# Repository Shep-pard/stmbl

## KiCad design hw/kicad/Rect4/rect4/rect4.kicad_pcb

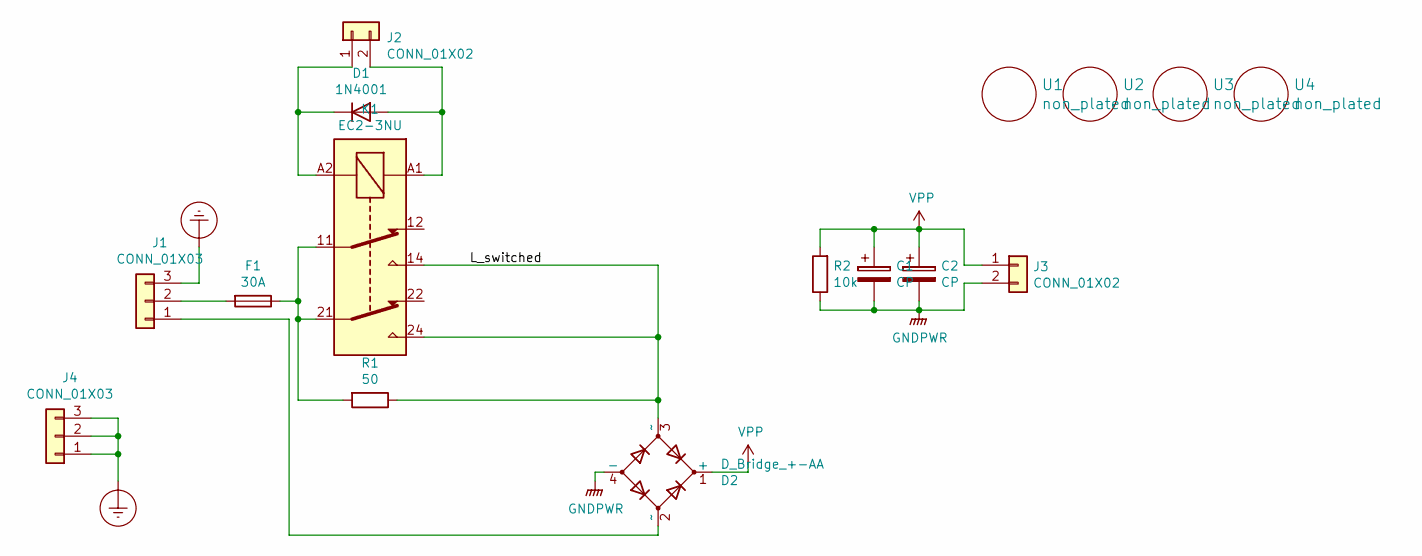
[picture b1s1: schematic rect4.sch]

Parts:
C1, C2: CP; C_Radial_D26_L45_P10
D1: 1N4001; D_DO-41_SOD81_P10.16mm_Horizontal
D2: D_Bridge_+-AA; Diode_Bridge_Vishay_KBU
F1: 30A; Fuse_Littelfuse_395Series
J1, J4: CONN_01X03; RM5.08_1x3
J2: CONN_01X02; RM3.5_1x2
J3: CONN_01X02; RM5.08_1x2
K1: EC2-3NU; Relay_DPDT_Finder_40.52
R1: 50; R_Axial_Power_L25.0mm_W9.0mm_P27.94mm
R2: 10k; R_Axial_DIN0207_L6.3mm_D2.5mm_P7.62mm_Horizontal
U1, U2, U3, U4: non_plated; non_plated_3mm

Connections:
/L_switched: D2.3 (~~), K1.14, K1.24, R1.1
Earth_Protective: J1.3, J4.1, J4.2, J4.3
GNDPWR: C1.2, C2.2, D2.4 (-), J3.2, R2.1
unnamed: D1.1 (K), J2.1, K1.A2
unnamed: D1.2 (A), J2.2, K1.A1
unnamed: D2.2 (~~), J1.1
unnamed: F1.1, K1.11, K1.21, R1.2
unnamed: F1.2, J1.2
VPP: C1.1, C2.1, D2.1 (+), J3.1, R2.2

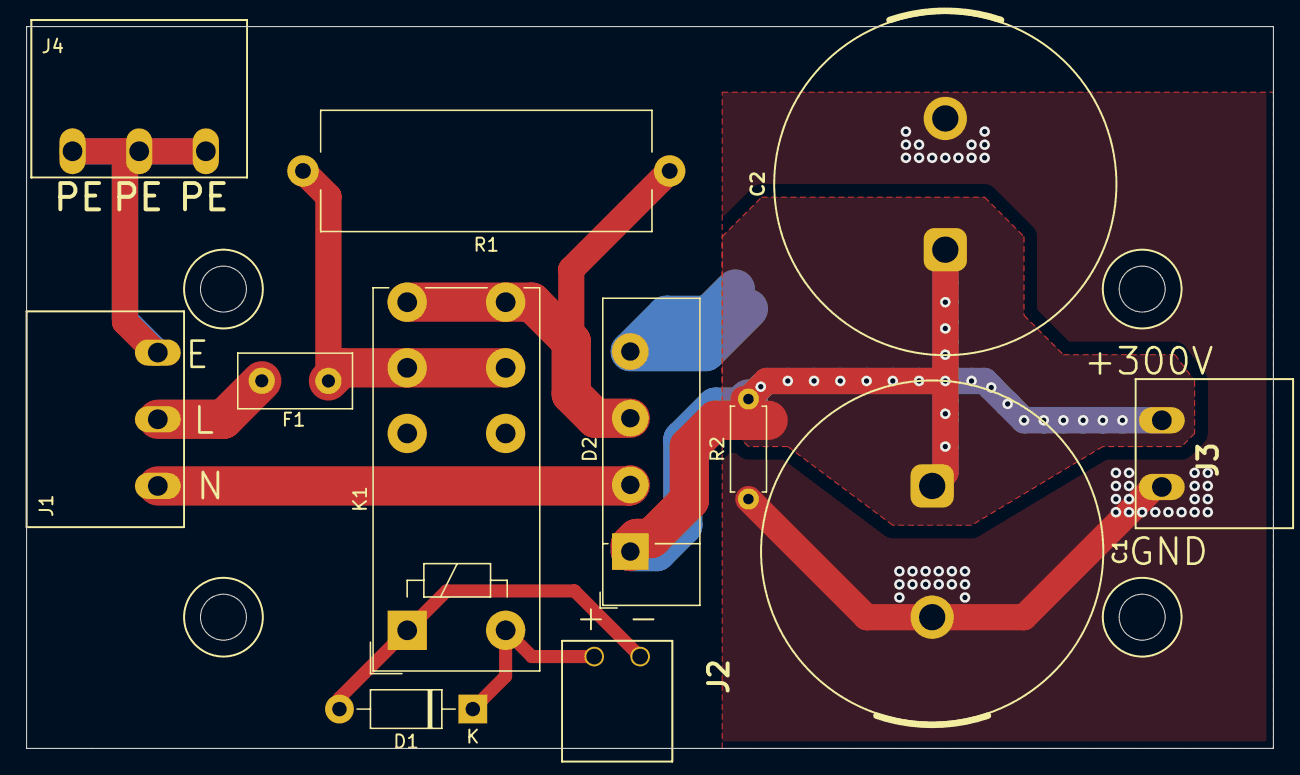
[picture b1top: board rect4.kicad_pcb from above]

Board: 2 copper layers, 95.0 x 55.0 mm, 16 parts (0 on the bottom side), 9 nets.

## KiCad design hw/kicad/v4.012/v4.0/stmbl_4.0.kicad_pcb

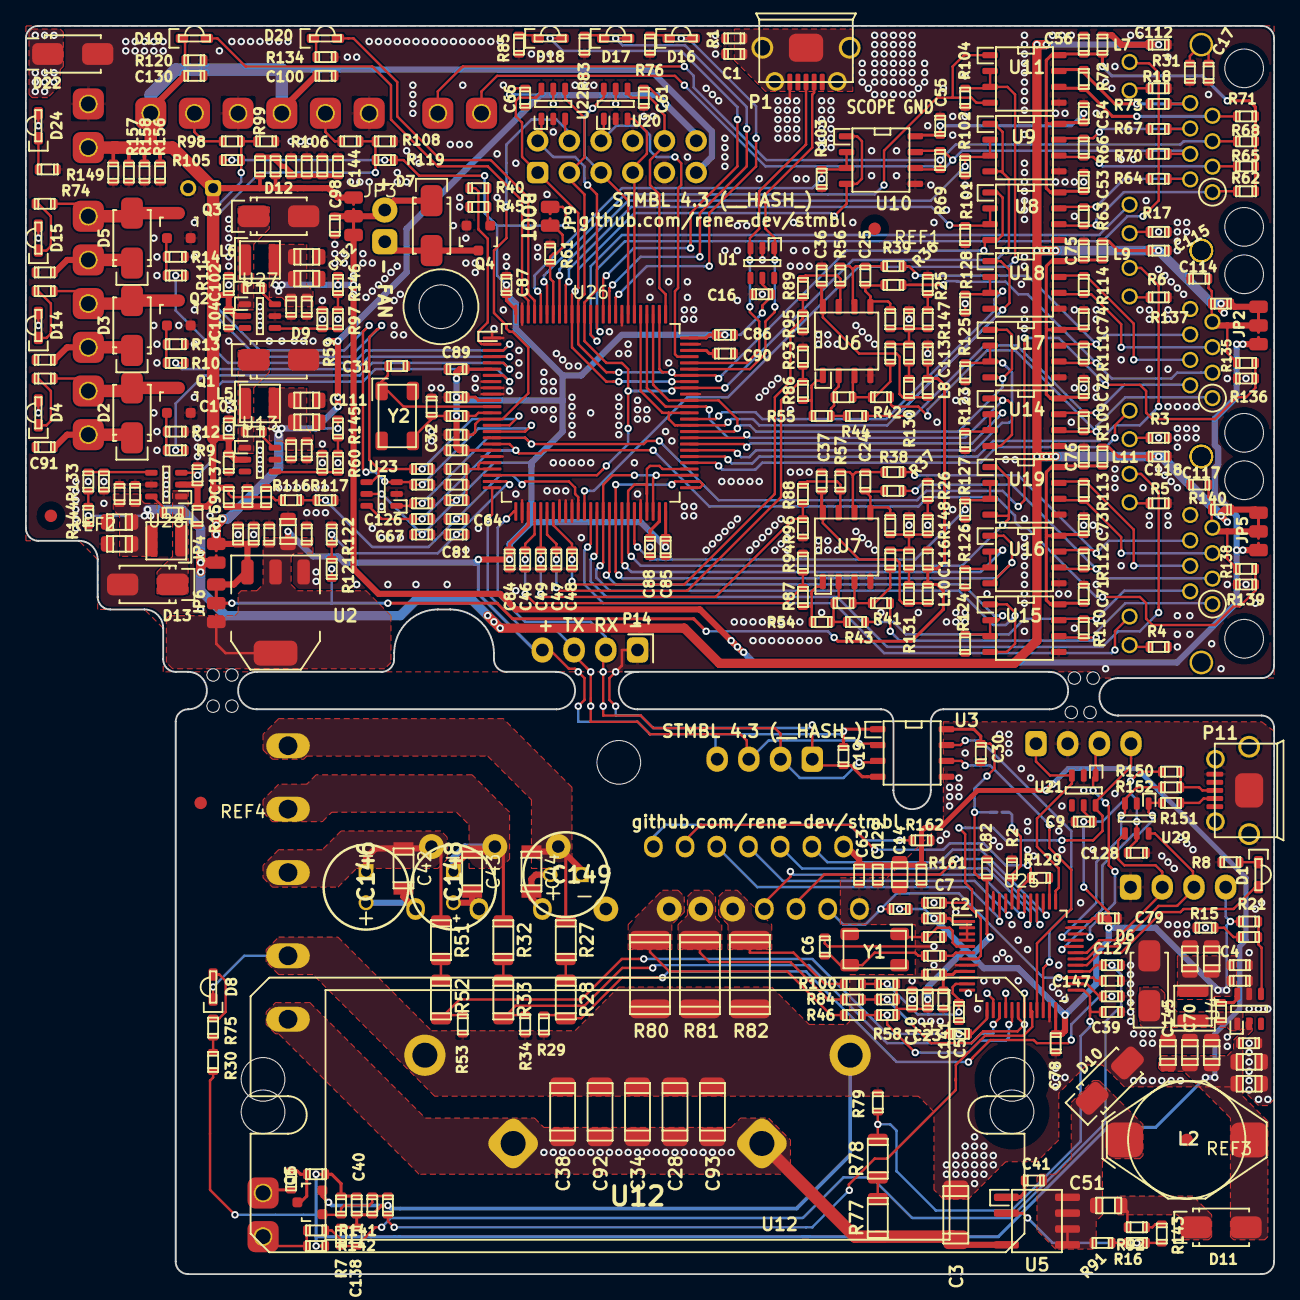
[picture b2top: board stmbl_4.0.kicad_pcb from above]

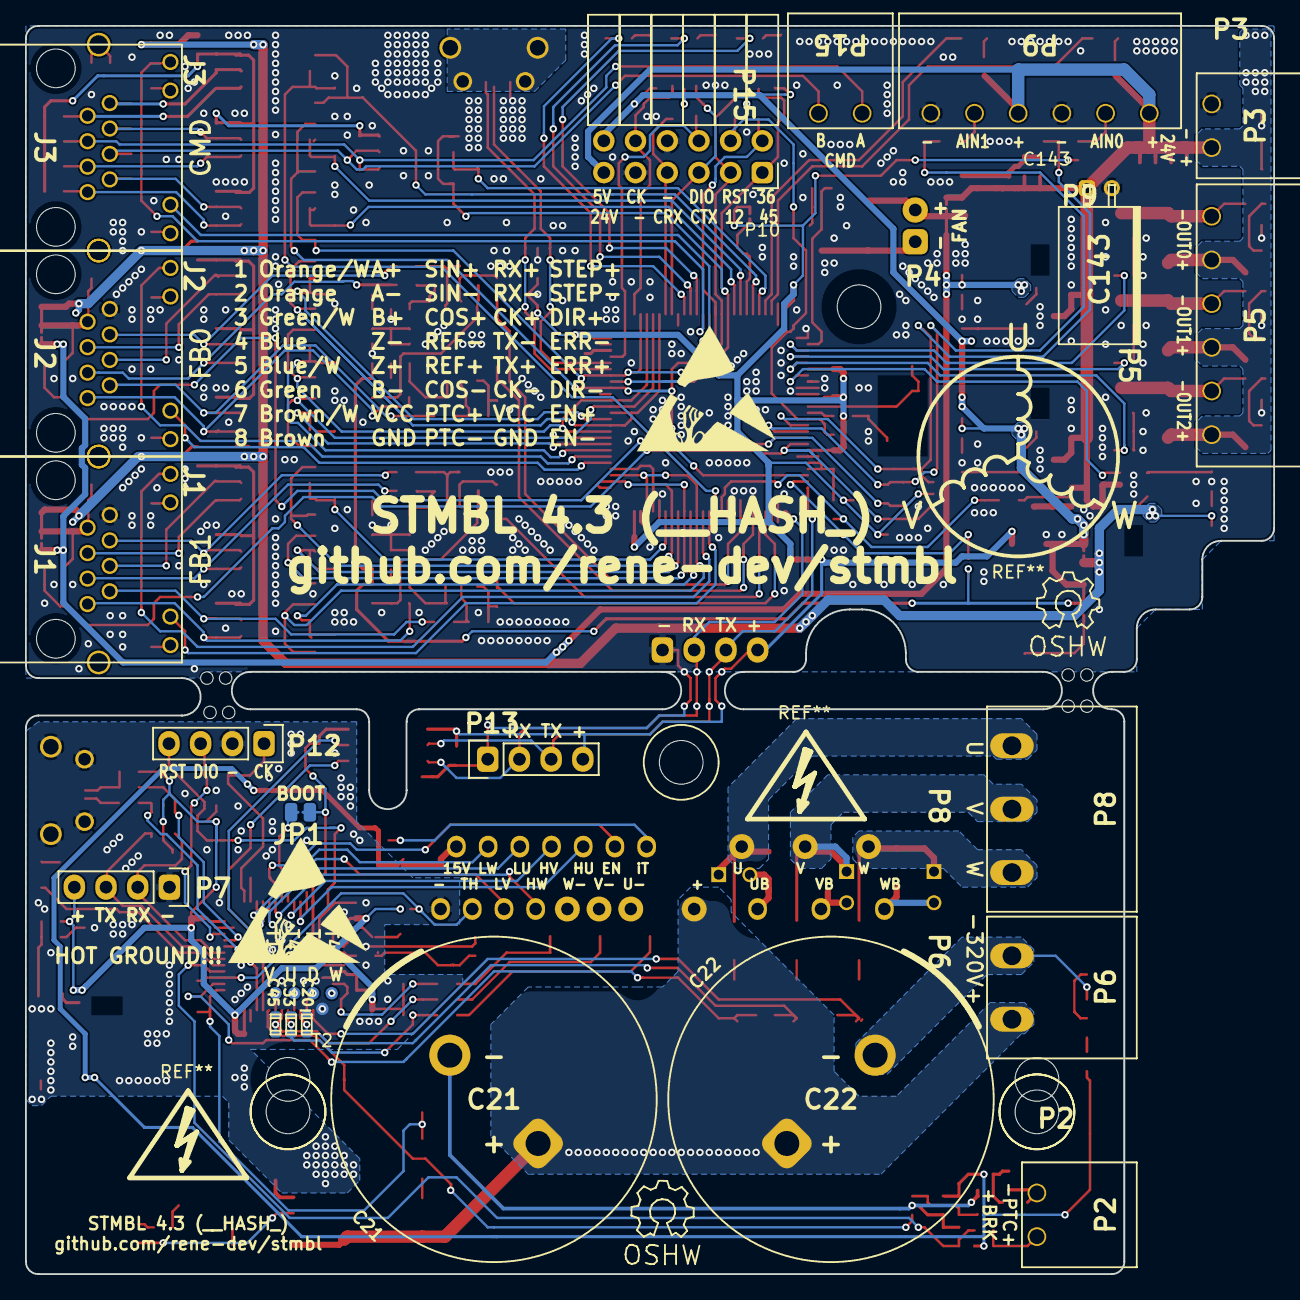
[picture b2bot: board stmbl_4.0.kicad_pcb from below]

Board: 2 copper layers, 100.0 x 100.0 mm, 435 parts (34 on the bottom side), 230 nets.

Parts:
C1, C2, C7, C9, C10, C12, C13, C15, C16, C17, C19, C29, C30, C36, C37, C40, C41, C53, C54, C55, C56, C58, C60, C61, C63, C66, C67, C71, C72, C73, C74, C75, C76, C77, C78, C79, C80, C82, C83, C84, C85, C86, C87, C89, C91, C94, C95, C96, C98, C99, C100, C103, C104, C105, C106, C107, C108, C112, C113, C114, C115, C116, C117, C118, C119, C120, C121, C122, C125, C126, C127, C128, C130, C138, C147: 100n; C_0603
C3, C28, C34, C38, C92, C93: 150n; C_1808
C4, C14, C35, C51, C68, C69, C70, C97, C109, C110, C111, C123, C124, C131, C132, C145: 10µ; C_0805
C5, C6, C11, C20, C23, C24, C25, C26, C27, C31, C32, C33, C39, C45, C57: 18p; C_0603
C8, C18, C50, C62, C65, C88, C90, C101, C102, C129, C133, C134, C135, C136, C137, C139, C140, C141, C142, C144: 2.2µ; C_0603
C21, C22: 270µ; C_Radial_D26_L45_P10
C42, C43, C44: 2.2µ; C_1206
C46, C47, C48, C49, C52, C59, C64, C81: 1n; C_0603
C143: 22µ; C_Radial_D6.5_L11_P2.5
C146, C148, C149: EKMG500ELL470MF11D; CAPPRD250W60D680H1250
D1, D16: red; LED-0805-SIDE
D2, D3, D5, D7, D10, D11: ES1J R2; SMA_Standard
D4, D8, D14, D15, D18, D19, D20, D24: green; LED-0805-SIDE
D6, D9, D12, D13: SS34A; SMA_Standard
D17: yellow; LED-0805-SIDE
D22: SMAJ24A TVS 24V; SMA_Standard
J1, J2, J3: RJ45_LED
JP1, JP4, JP9: Jumper_NO_Small; SOLDER_JUMPER
JP2, JP3, JP5, JP6: JUMPER3_NC; SOLDER_JUMPER_3_NC
L1, L3, L7, L8, L9, L10, L11: 220r 700mA; R_0603
L2: 1m 250mA; NPI31W
L4, L6: 10µH 1A; SMD_INDUCTOR_32x25
L5, L12: 4.7µH 1.5A; SMD_INDUCTOR_32x25
LOGO1, LOGO1#2: OPEN_HARDWARE_1; Symbol_OSHW-Logo_SilkScreen
P1, P11: USB_OTG; USB_Micro-B
P2, P3, P15: CONN_01X02; RM3.5_1x2
P4: CONN_01X02; Pin_Header_Angled_1x02
P5, P9: CONN_01X06; RM3.5_1x6
P6: CONN_01X02; RM5.08_1x2
P7, P12: CONN_01X04; Pin_Header_Straight_1x04
P8: CONN_01X03; RM5.08_1x3
P10: CONN_02X06; Socket_Strip_Angled_2x06
P13: CONN_01X04; Socket_Strip_Straight_1x04
P14: CONN_01X04; Pin_Header_Angled_1x04
Q1, Q2, Q3, Q4, Q5: IRLML6344; SOT-23
R1, R23, R24, R25, R26, R31, R109, R110, R111, R112, R113, R114, R130, R131: 120; R_0603
R2, R12, R13, R14, R15, R16, R30, R45, R61, R63, R66, R69, R72, R75, R91, R99, R101, R102, R103, R104, R105, R108, R117, R118, R119, R121, R122, R123, R124, R125, R126, R127, R128, R129, R136, R139, R145, R153, R162, R165: 1k; R_0603
R3, R4, R5, R6, R8, R17, R18, R46, R76, R83, R84, R85, R93, R94, R95, R96, R100, R120, R134: 470; R_0603
R7, R35, R36, R37, R38, R39, R41, R42, R43, R44, R62, R64, R65, R67, R68, R70, R71, R73, R98, R106, R115, R116, R132, R135, R137, R138, R140, R142, R155, R156, R157, R158: 10k; R_0603
R9, R10, R11, R40, R86, R87, R88, R89, R147, R148, R151, R152, R154, R159, R160, R163, R167: 22; R_0603
R19, R47, R48, R49, R50, R54, R55, R56, R57, R58, R90, R92, R107: 15k; R_0603
R20, R22, R29, R34, R53, R59, R74, R79, R144, R146, R149, R161, R164, R166: 3.9k; R_0603
R21, R60, R97, R133, R141: 51k; R_0603
R27, R28, R32, R33, R51, R52, R77, R78: 249k; R_1206
R80, R81, R82: 0.003; R_2512
R143, R150: 1.5k; R_0603
REF1, REF2, REF3, REF4: Fiducial_1mm_Dia_2.54mm_Outer_CopperTop; Fiducial_1mm_Outer_CopperTop
T1, T2, T44, T45, T46: testpoint; Measurement_Point_Round-SMD-Pad_Small
U1, U20, U21, U22, U23, U29: USBLC6-4SC6; SOT-23-6
U2: zldo1117; SOT-223
U3: SI8621; SOIC-8-N
U4, U13, U27, U28: ACT4088; SOT-23-6
U5: LNK304D; SOIC-7
U6, U7: LM358; SOIC-8-N
U8, U9, U10, U11, U14, U15, U16, U17, U18, U19: SN65176B; SOIC-8-N
U12: IRAM256a; IRAM256
U24, U24#2, U30, U31, U31#2, U32: non_plated; non_plated_3mm
U25: STM32F303CBTx; LQFP-48_7x7mm_Pitch0.5mm
U26: STM32F405VG; LQFP-100_14x14mm_Pitch0.5mm
U33: heatsink; non_plated_1mm
U34: fan; non_plated_1mm
U35, U36, U36#2, U36#3, U37, U39: non_plated; non_plated_1mm
Y1, Y2: 8M; Crystal_SMD_0503_4Pads

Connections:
+3.3VP: C2.1, C4.1, C9.1, C10.2, C30.2, C35.1, C50.1, C60.1, C78.2, C79.2, C82.2, C128.1, JP1.1, L1.2, L4.2, P7.4, R21.1, R58.2, R90.2, R107.2, R115.1, R150.2, U3.8, U21.5, U25.1, U25.2, U25.3, U25.4, U25.24, U25.36, U25.48, U29.5
+3V3: C16.2, C18.1, C19.1, C67.1, C77.2, C80.2, C84.2, C85.2, C86.2, C87.2, C89.2, C99.1, C131.1, JP6.3, JP9.1, L3.2, P13.4, P14.4, R105.1, R119.1, U1.5, U2.2, U3.1, U23.5, U26.6, U26.11, U26.19, U26.28, U26.50, U26.75, U26.100
+5F: C112.1, C115.2, C118.2, C122.1, C123.1, C124.1, C134.1, JP2.1, JP4.1, JP5.1, L7.2, L9.1, L11.1, L12.2, R137.2, R140.2, R144.1
+5V: C8.1, C61.1, C66.1, C96.1, C107.1, C109.1, C111.1, C135.1, JP4.2, JP6.1, L5.2, P10.12, R145.1, U2.3, U20.5, U22.5
+5VA: C113.2, C116.2, JP6.2, L8.1, L10.1, R121.1
+12V: C108.1, C110.1, C132.1, C136.1, JP2.3, JP3.1, JP5.3, L6.2, R146.1
+15V: C14.2, C40.2, C58.1, C63.1, C68.1, C69.1, C70.1, C97.1, C129.1, C145.1, D11.2, L2.2, R30.1, R142.1, R161.1, R164.1, R166.1, U4.2, U12.28
+24V: C91.1, C94.1, C95.1, C100.1, C102.1, C103.1, C104.1, C120.1, C130.1, C133.1, C137.1, C143.1, D2.1, D3.1, D4.2, D5.1, D14.2, D15.2, D22.1, D24.2, JP3.3, P3.1, P5.1, P5.3, P5.5, P9.1, P9.4, P10.11, R116.1, R154.1, R155.1, R156.1, R157.1, R158.1, R159.1, R160.1, U13.2, U27.2, U28.2
/ctrl/FB0/A12: C47.1, R86.1, R93.1, U26.31
/ctrl/FB0/A35: C48.1, R89.1, R95.1, U26.32
/ctrl/FB0/A78: C125.1, R135.2, R136.1, U23.1, U26.17
/ctrl/FB0/D12: U14.1, U14.4, U26.59, U26.64, U26.79
/ctrl/FB0/D36: U17.1, U17.4, U26.60, U26.65, U26.78
/ctrl/FB0/D45: U18.1, U18.4, U26.61, U26.63, U26.80
/ctrl/FB0/E12: R123.1, U14.2, U14.3, U26.58
/ctrl/FB0/E36: R125.1, U17.2, U17.3, U26.57
/ctrl/FB0/E45: R128.1, U18.2, U18.3, U26.62
/ctrl/FB1/A12: C46.1, R87.1, R94.1, U26.29
/ctrl/FB1/A35: C49.1, R88.1, R96.1, U26.30
/ctrl/FB1/A78: C126.1, R138.2, R139.1, U23.6, U26.18
/ctrl/FB1/D12: U15.1, U15.4, U26.40, U26.48, U26.53
/ctrl/FB1/D36: U16.1, U16.4, U26.42, U26.51, U26.52
/ctrl/FB1/D45: U19.1, U19.4, U26.44, U26.47, U26.54
/ctrl/FB1/E12: R124.1, U15.2, U15.3, U26.41
/ctrl/FB1/E36: R126.1, U16.2, U16.3, U26.43
/ctrl/FB1/E45: R127.1, U19.2, U19.3, U26.45
/ctrl/IO/CAN_RX: P10.7, U20.3, U26.81
/ctrl/IO/CAN_TX: P10.5, U20.6, U26.82
/ctrl/IO/IO_FAN: R40.2, U26.2
/ctrl/IO/IO_GREEN: D18.2, U26.86
/ctrl/IO/IO_L0: D19.2, U26.98
/ctrl/IO/IO_L1: D20.2, U26.97
/ctrl/IO/IO_OUT0: R11.2, U26.3
/ctrl/IO/IO_OUT1: R10.2, U26.4
/ctrl/IO/IO_OUT2: R9.2, U26.5
/ctrl/IO/IO_RED: D16.2, U26.84
/ctrl/IO/IO_YELLOW: D17.2, U26.85
/ctrl/IO/NRST: C29.2, P10.4, U22.3, U26.14
/ctrl/IO/SWCK: P10.10, U20.4, U26.76
/ctrl/IO/SWDIO: P10.6, U20.1, U26.72
/ctrl/RX: P13.2, P14.2, U3.3, U26.26
/ctrl/TX: P13.3, P14.3, U3.2, U26.25
/ctrl/f4/A_5V: C81.1, R121.2, R122.1, U26.24
/ctrl/f4/A_24V: C64.1, R116.2, R117.1, U26.36
/ctrl/f4/CMD_12: P10.3, U8.1, U8.4, U22.4, U26.69, U26.77, U26.90
/ctrl/f4/CMD_12E: R101.1, U8.2, U8.3, U26.92
/ctrl/f4/CMD_36: P10.2, U9.1, U9.4, U22.1, U26.23, U26.67, U26.89
/ctrl/f4/CMD_36E: R102.1, U9.2, U9.3, U26.93
/ctrl/f4/CMD_45: P10.1, U10.1, U10.4, U22.6, U26.68, U26.91
/ctrl/f4/CMD_45E: R103.1, U10.2, U10.3, U26.96
/ctrl/f4/CMD_78: U11.1, U11.4, U26.95
/ctrl/f4/CMD_78E: R104.1, U11.2, U11.3, U26.37
/ctrl/f4/CMD_L1: J3.12, U26.88
/ctrl/f4/CMD_L2: J3.10, U26.87
/ctrl/f4/EN_5V: U26.7, U28.3
/ctrl/f4/FB0_L1: J2.12, U26.55
/ctrl/f4/FB0_L2: J2.10, U26.56
/ctrl/f4/FB1_L1: J1.12, U26.38
/ctrl/f4/FB1_L2: J1.10, U26.39
/ctrl/f4/IO_AIN0: C52.1, R98.2, R99.1, R105.2, U23.4, U26.15
/ctrl/f4/IO_AIN1: C59.1, R106.2, R108.1, R119.2, U23.3, U26.16
/hv/back-emf/U: C44.1, C149.1, P8.1, R27.1, U12.10
/hv/back-emf/V: C43.1, C148.1, P8.2, R32.1, U12.6
/hv/back-emf/W: C42.1, C146.1, P8.3, R51.1, U12.2
/hv/cur/A_IU: C33.1, R46.1, R58.1, U25.17
/hv/cur/A_IV: C45.1, R84.1, R90.1, U25.18
/hv/cur/A_IW: C57.1, R100.1, R107.1, U25.11
/hv/driver/CUH: R46.2, R80.1, U12.17
/hv/driver/CVH: R81.1, R84.2, U12.19
/hv/driver/CWH: R82.1, R100.2, U12.21
/hv/driver/HU: U12.20, U25.46
/hv/driver/HV: U12.22, U25.45
/hv/driver/HW: U12.23, U25.42
/hv/driver/LU: U12.24, U25.41
/hv/driver/LV: U12.25, U25.40
/hv/driver/LW: U12.26, U25.39
/hv/driver/itirp: R162.1, U12.16
/hv/f3/A_HV: C39.1, R78.2, R79.1, U25.25
/hv/f3/A_T_HV: C147.1, R115.2, U12.27, U25.27
/hv/f3/A_T_MOT: C127.2, C138.2, R7.2, R141.2, U25.28
/hv/f3/A_U: C11.1, R28.2, R29.1, U25.26
/hv/f3/A_V: C20.1, R33.2, R34.1, U25.15
/hv/f3/A_W: C23.1, R52.2, R53.1, U25.13
/hv/f3/BRK: R163.1, U25.20
/hv/f3/HV_EN: R129.1, U12.18, U25.43
/hv/f3/HV_RX: U3.7, U25.22
/hv/f3/HV_TX: U3.6, U25.21
/hv/f3/IO_RX: P7.2, U25.31, U29.4
/hv/f3/IO_TX: P7.3, U25.30, U29.6
/hv/f3/NRST: C7.1, P12.4, U21.6, U25.7
/hv/f3/SWCLK: P12.1, U21.3, U25.37
/hv/f3/SWDIO: P12.3, U21.1, U25.34
/hv/f3/USB_DM: R151.1, U25.32, U29.1
/hv/f3/USB_DP: R152.1, U25.33, U29.3
GND: C1.2, C8.2, C12.2, C13.2, C16.1, C17.2, C18.2, C19.2, C29.1, C31.2, C32.2, C36.1, C37.1, C46.2, C47.2, C48.2, C49.2, C52.2, C53.2, C54.2, C55.2, C56.2, C59.2, C61.2, C62.2, C64.2, C65.1, C66.2, C67.2, C71.2, C72.2, C73.2, C74.2, C75.2, C76.2, C77.1, C80.1, C81.2, C84.1, C85.1, C86.1, C87.1, C88.2, C89.1, C90.2, C91.2, C94.2, C95.2, C96.2, C98.2, C99.2, C100.2, C101.2, C102.2, C103.2, C104.2, C107.2, C108.2, C109.2, C110.2, C111.2, C112.2, C113.1, C114.2, C115.1, C116.1, C117.2, C118.1, C119.1, C120.2, C122.2, C123.2, C124.2, C125.2, C126.2, C130.2, C131.2, C132.2, C133.2, C134.2, C135.2, C136.2, C137.2, C139.2, C140.2, C142.2, C143.2, C144.2, D9.2, D12.2, D13.2, D22.2, J1.8, J2.8, P1.5, P3.2, P9.3, P9.6, P10.8, P10.9, P13.1, P14.1, Q1.2, Q2.2, Q3.2, Q4.2, R1.2, R3.2, R4.2, R5.2, R6.2, R12.2, R13.2, R14.2, R17.2, R18.2, R25.2, R26.2, R31.2, R35.2, R45.2, R59.2, R61.1, R64.2, R67.2, R70.2, R73.2, R76.2, R83.2, R85.2, R93.2, R94.2, R95.2, R96.2, R99.2, R101.2, R102.2, R103.2, R104.2, R108.2, R117.2, R120.2, R122.2, R123.2, R124.2, R125.2, R126.2, R127.2, R128.2, R132.2, R134.2, R136.2, R139.2, R149.2, R155.2, R156.2, R157.2, R158.2, U1.2, U2.1, U3.4, U6.4, U7.4, U8.5, U9.5, U10.5, U11.5, U13.5, U14.5, U15.5, U16.5, U17.5, U18.5, U19.5, U20.2, U22.2, U23.2, U26.1, U26.8, U26.9, U26.10, U26.20, U26.27, U26.33, U26.34, U26.35, U26.46, U26.66, U26.74, U26.83, U26.99, U27.5, U28.5
GNDD: C17.1, J1.13, J2.13, J3.13, R31.1
GNDPWR: C2.2, C3.2, C4.2, C5.2, C6.2, C7.2, C9.2, C10.1, C11.2, C14.1, C20.2, C21.2, C22.2, C23.2, C28.2, C30.1, C33.2, C34.2, C35.2, C38.2, C39.2, C40.1, C45.2, C50.2, C57.2, C58.2, C60.2, C63.2, C68.2, C69.2, C70.2, C78.1, C79.1, C82.1, C83.1, C92.2, C93.2, C97.2, C127.1, C128.2, C129.2, C138.1, C141.1, C145.2, C147.2, D6.2, D8.1, D10.2, P6.1, P7.1, P11.5, P11.6, P12.2, Q5.2, R2.2, R7.1, R8.1, R15.2, R29.2, R34.2, R53.2, R79.2, R80.2, R81.2, R82.2, R161.2, R162.2, R165.2, T2.1, U3.5, U4.5, U12.29, U21.2, U25.8, U25.10, U25.23, U25.35, U25.47, U29.2
unnamed: C1.1, P1.6, R1.1
unnamed: C5.1, U25.5, Y1.1
unnamed: C6.1, R118.2, Y1.2
unnamed: C12.1, R23.2, R48.1, R49.1, R148.1
unnamed: C13.1, R24.2, R47.1, R50.1, R147.1
unnamed: C15.1, U4.6
unnamed: C15.2, D6.1, L4.1, U4.1
unnamed: C24.1, R37.1, R49.2, U7.5
unnamed: C24.2, R38.1, R57.2, U7.6
unnamed: C25.1, R36.1, R50.2, U6.5
unnamed: C25.2, R39.1, R56.2, U6.6
unnamed: C26.1, R41.1, R48.2, U7.3
unnamed: C26.2, R43.1, R54.2, U7.2
unnamed: C27.1, R42.1, R47.2, U6.3
unnamed: C27.2, R44.1, R55.2, U6.2
unnamed: C31.1, U26.12, Y2.1
unnamed: C32.1, R153.2, Y2.2
unnamed: C36.2, L8.2, R130.1, U6.8
unnamed: C37.2, L10.2, R131.1
unnamed: C41.1, U5.1
unnamed: C41.2, C51.2, D10.1, L2.1, R91.1, U5.5, U5.6, U5.7, U5.8
unnamed: C51.1, D11.1, R92.2
unnamed: C53.1, C54.1, C55.1, C56.1, L7.1, R62.1, R65.1, R68.1, R71.1, U8.8, U9.8, U10.8, U11.8
unnamed: C71.1, C73.1, C76.1, L11.2, U15.8, U16.8, U19.8
unnamed: C72.1, C74.1, C75.1, L9.2, U14.8, U17.8, U18.8
unnamed: C88.1, U26.49
unnamed: C90.1, U26.73
unnamed: C98.1, D7.1, JP3.2, P4.2
unnamed: C62.1, C101.1, R159.2
unnamed: C105.1, U13.6
unnamed: C105.2, D9.1, L5.1, U13.1
unnamed: C106.1, U27.6
unnamed: C106.2, D12.1, L6.1, U27.1
unnamed: C114.1, J2.7, JP2.2, R135.1, R137.1
unnamed: C117.1, J1.7, JP5.2, R138.1, R140.1
unnamed: C65.2, C119.2, L3.1, U26.21, U26.22
unnamed: C121.1, U28.6
unnamed: C121.2, D13.1, L12.1, U28.1
unnamed: C139.1, C140.1, C142.1, C144.1, R154.2, R160.2
unnamed: C83.2, C141.2, L1.1, U25.9
unnamed: C42.2, C146.2, U12.1
unnamed: C43.2, C148.2, U12.5
unnamed: C44.2, C149.2, U12.9
unnamed: D1.1, R8.2
unnamed: D1.2, U25.29
unnamed: D2.2, P5.2, Q1.3, R20.2
unnamed: D3.2, P5.4, Q2.3, R22.2
unnamed: D4.1, R20.1
unnamed: D5.2, P5.6, Q3.3, R74.2
unnamed: D7.2, P4.1, Q4.3
unnamed: D8.2, R75.2
unnamed: D14.1, R22.1
unnamed: D15.1, R74.1
unnamed: D16.1, R76.1
unnamed: D17.1, R83.1
unnamed: D18.1, R85.1
unnamed: D19.1, R120.1
unnamed: D20.1, R134.1
unnamed: D24.1, R149.1
unnamed: J1.1, R41.2, R110.1, U15.6
unnamed: J1.2, R43.2, R110.2, U15.7
unnamed: J1.3, R37.2, R112.1, U16.6
unnamed: J1.4, R113.2, U19.7
unnamed: J1.5, R113.1, U19.6
unnamed: J1.6, R38.2, R112.2, U16.7
unnamed: J1.9, R5.1
unnamed: J1.11, R4.1
unnamed: J2.1, R42.2, R109.1, U14.6
unnamed: J2.2, R44.2, R109.2, U14.7
unnamed: J2.3, R36.2, R111.1, U17.6
unnamed: J2.4, R114.2, U18.7
unnamed: J2.5, R114.1, U18.6
unnamed: J2.6, R39.2, R111.2, U17.7
unnamed: J2.9, R6.1
unnamed: J2.11, R3.1
unnamed: J3.1, R62.2, R63.1, U8.6
unnamed: J3.2, R63.2, R64.1, U8.7
unnamed: J3.3, R65.2, R66.1, U9.6
unnamed: J3.4, P15.2, R69.2, R70.1, U10.7
unnamed: J3.5, P15.1, R68.2, R69.1, U10.6
unnamed: J3.6, R66.2, R67.1, U9.7
unnamed: J3.7, R71.2, R72.1, U11.6
unnamed: J3.8, R72.2, R73.1, U11.7
unnamed: J3.9, R18.1
unnamed: J3.11, R17.1
unnamed: JP1.2, R2.1, U25.44
unnamed: JP9.2, R61.2, U26.94
unnamed: P1.2, U1.1, U26.70
unnamed: P1.3, U1.3, U26.71
unnamed: P2.1, R141.1, R142.2
unnamed: P2.2, R167.2
unnamed: P9.2, R98.1
unnamed: P9.5, R106.1
unnamed: P11.2, R151.2
unnamed: P11.3, R150.1, R152.2
unnamed: Q1.1, R9.1, R12.1
unnamed: Q2.1, R10.1, R13.1
unnamed: Q3.1, R11.1, R14.1
unnamed: Q4.1, R40.1, R45.1
unnamed: Q5.1, R163.2, R164.2, R165.1
unnamed: Q5.3, R166.2, R167.1
unnamed: R15.1, R19.2
unnamed: R16.1, R91.2
unnamed: R19.1, R21.2, U4.4
unnamed: R27.2, R28.1
unnamed: R30.2, R75.1
unnamed: R32.2, R33.1
unnamed: R35.1, R60.2, U13.4
unnamed: R51.2, R52.1
unnamed: R54.1, R87.2, U7.1
unnamed: R55.1, R86.2, U6.1
unnamed: R56.1, R89.2, U6.7
unnamed: R57.1, R88.2, U7.7
unnamed: R59.1, R97.2, U27.4
unnamed: R77.2, R78.1
unnamed: R118.1, U25.6
unnamed: R129.2, U25.38
unnamed: R24.1, R130.2
unnamed: R23.1, R131.2
unnamed: R132.1, R133.2, U28.4
unnamed: R133.1, R144.2
unnamed: R16.2, R143.1, U5.2
unnamed: R92.1, R143.2
unnamed: R60.1, R145.2
unnamed: R97.1, R146.2
unnamed: R25.1, R147.2
unnamed: R26.1, R148.2
unnamed: R153.1, U26.13
unnamed: T1.1, U25.19
unnamed: T44.1, U25.12
unnamed: T45.1, U25.14
unnamed: T46.1, U25.16
VPP: C3.1, C21.1, C22.1, C28.1, C34.1, C38.1, C92.1, C93.1, P6.2, R77.1, U5.4, U12.13

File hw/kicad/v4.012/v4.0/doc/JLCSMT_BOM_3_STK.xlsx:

Comment | Designator | Footprint | LCSC Part #
100nF | C19,C30,C127,C138,C40,C78,C79,C82,C83,C2,C7,C10,C9,C128,C58,C41,C15,C60,C63,C14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 | 0603_C | C14663
10uF | C51,C35,C68,C69,C4,C97,C70,C145,C14,C110,C109,C111,C123,C124,C132,C131 | 0805_C | C15850
18pF | C5,C6,C11,C23,C39,C57,C25,C27,C24,C26,C31,C32 | 0603_C | C1647
2.2uF | C141,C50,C129,C18,C8,C101,C102,C136,C135,C134,C137,C133,C62,C139,C140,C142,C144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 | 0603_C | C23630
100nF | C42,C43,C44, | 1206_C | C24497
1nF | C47,C48,C46,C49,C52,C59,C81,C64 | 0603_C | C1588
120? | R31,R109,R111,R114,R24,R25,R130,R110,R112,R113,R23,R26,R131,R1 | 0603_R | C22787
1K? | R162,R165,R2,R129,R118,R91,R75,R30,R15,R16,R145,R63,R66,R69,R72,R101,R102,R103,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 | 0603_R | C21190
470? | R8,R46,R84,R100,R17,R18,R3,R6,R93,R95,R4,R5,R94,R96,R134,R120,R85,R83,R76 | 0603_R | C23179
10K? | R142,R7,R115,R35,R132,R158,R155,R156,R157,R62,R64,R65,R67,R68,R70,R71,R73,R42,R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 | 0603_R | C25804
22? | R163,R167,R151,R152,R154,R159,R160,R86,R89,R147,R87,R88,R148,R9,R10,R11,R40 | 0603_R | C23345
15K? | R92,R19,R58,R90,R107,R47,R55,R50,R56,R48,R54,R49,R57 | 0603_R | C22809
3.9K? | R164,R166,R161,R29,R34,R53,R79,R59,R146,R144,R149,R20,R22,R74 | 0603_R | C23018
51K? | R141,R21,R97,R60,R133 | 0603_R | C23196
249K? | R27,R28,R32,R33,R51,R52,R77,R78 | 1206_R | C37158
1.5K? | R143,R150 | 0603_R | C22843
LM358 | U6,U7 | SOIC-8-N | C7950
SN65176B | U8,U9,U10,U11,U14,U17,U18,U15,U16,U19 | SOIC-8-N | C31302
STM32F303CBTx | U25 | LQFP-48_7x7mm_Pitch0.5mm | C108516
STM32F405VG | U26 | LQFP-100_14x14mm_Pitch0.5mm | C56621
USBLC6-4SC6 | U21,U29,U1,U23,U20,U22 | SOT-23-6 | C252436
ES1J R2 | D10,D11,D2,D3,D5,D7 | DO-214AC | C84166
220r 700mA | L1,L7,L8,L9,L10,L11,L3 | 0603_R | C98286
SS34A | D6,D12,D9,D13 | stmbl:SMA_Standard | C183891
IRLML6344 | Q5,Q1,Q2,Q3,Q4 | stmbl:SOT-23 | C53550

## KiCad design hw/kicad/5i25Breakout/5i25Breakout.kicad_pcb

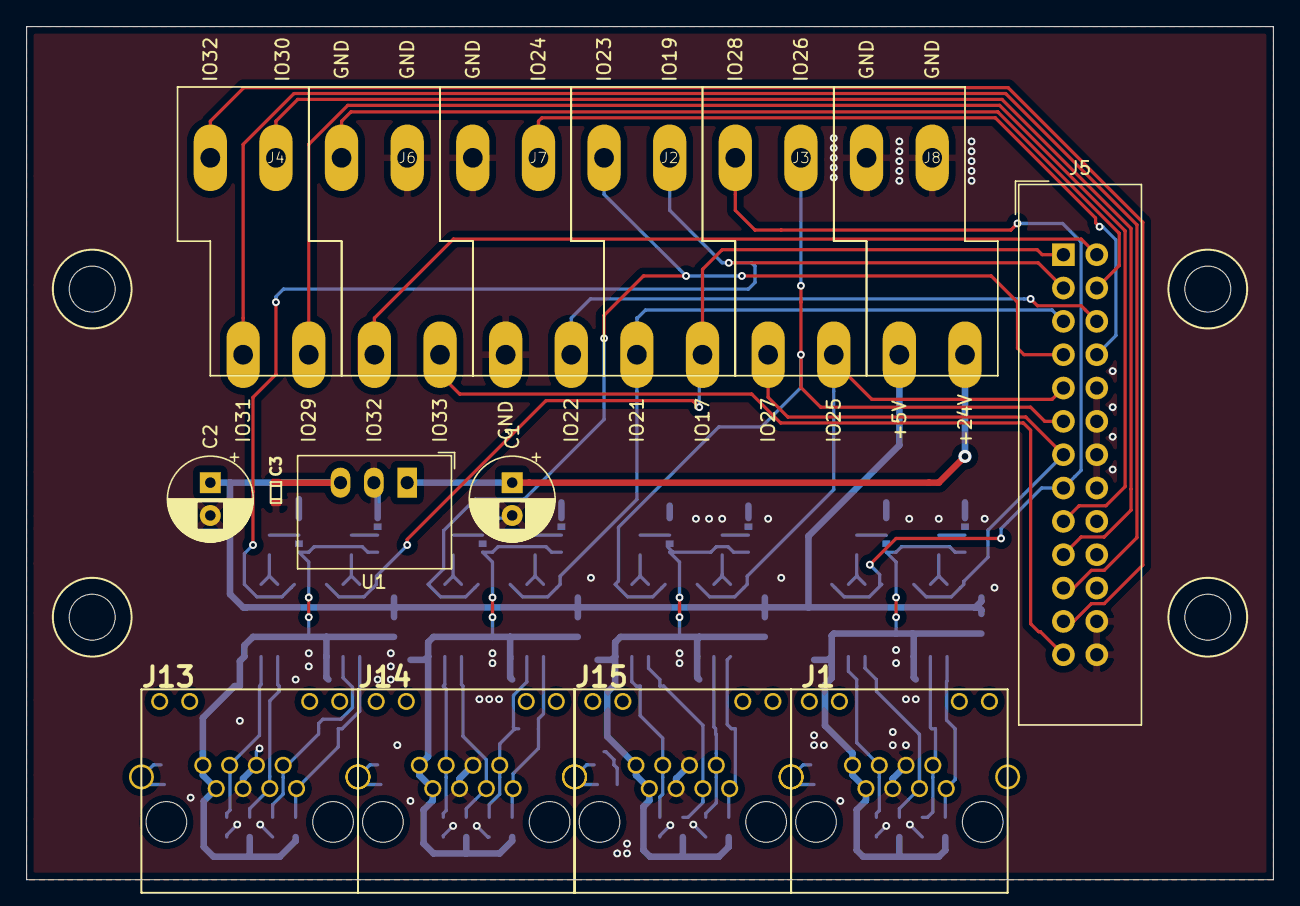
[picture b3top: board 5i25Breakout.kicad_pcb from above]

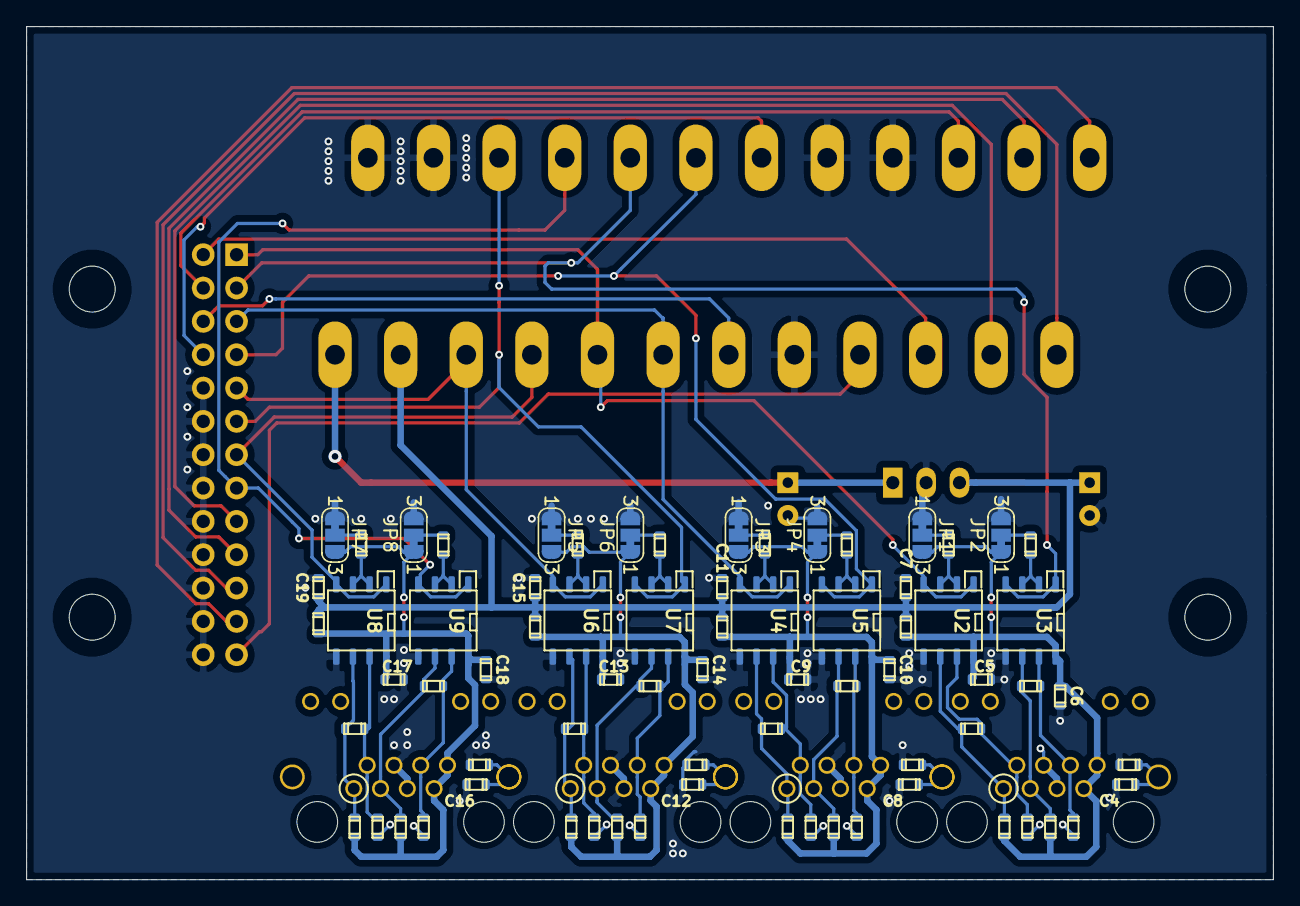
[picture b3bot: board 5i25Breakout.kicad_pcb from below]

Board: 2 copper layers, 95.0 x 65.0 mm, 91 parts (72 on the bottom side), 57 nets.

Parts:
C1, C2: 22uF; CP_Radial_D6.3mm_P2.50mm
C3, C4, C5, C6, C7, C8, C9, C10, C11, C12, C13, C14, C15, C16, C17, C18, C19: 100n; C_0603
J1, J13, J14, J15: RJ45_LED
J2, J3, J4, J6, J7, J8: Conn_01x04; TERMINAL_BLOCK_2PIN_5
J5: Conn_02x13_Odd_Even; IDC-Header_2x13_P2.54mm_Vertical
JP1, JP2, JP3, JP4, JP5, JP6, JP7, JP8: JUMPER3_NC; SolderJumper-3_P1.3mm_Bridged12_RoundedPad1.0x1.5mm_NumberL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
L1, L2, L3, L4: 220r 700mA; R_0603
R1, R10, R19, R28: 120; R_0603
R2, R4, R5, R7, R11, R13, R14, R16, R20, R22, R23, R25, R29, R31, R32, R34: 10k; R_0603
R3, R6, R8, R9, R12, R15, R17, R18, R21, R24, R26, R27, R30, R33, R35, R36: 1k; R_0603
U1: R-78C5.0-1.0; Converter_DCDC_RECOM_R-78E-0.5_THT
U2, U3, U4, U5, U6, U7, U8, U9: SN65176B; SOIC-8-N
U10, U11, U12, U13: non_plated; non_plated_3mm

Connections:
+5F: C2.1, C3.1, C7.1, C11.1, C15.1, C19.1, J8.3, L1.2, L2.2, L3.2, L4.2, U1.3
+24V: C1.1, J8.1, U1.1
/IO17: J2.1, J5.1, U2.1, U2.4
/IO18: J5.2, J6.3
/IO19: J2.2, J5.3, U3.1, U3.4
/IO20: J5.4, J6.4
/IO21: J2.3, J5.5, U4.1, U4.4
/IO22: J5.6, J7.1
/IO23: J2.4, J5.7, U5.1, U5.4
/IO24: J5.8, J7.2
/IO25: J3.1, J5.9, U6.1, U6.4
/IO26: J3.2, J5.11, U7.1, U7.4
/IO27: J3.3, J5.13, U8.1, U8.4
/IO28: J3.4, J5.15, U9.1, U9.4
/IO29: J4.1, J5.17
/IO30: J4.2, J5.19
/IO31: J4.3, J5.21
/IO32: J4.4, J5.23
/IO33: J5.25, J6.1
/RJ45/DIR1: R8.1, U2.2, U2.3
/RJ45/DIR2: R9.1, U3.2, U3.3
/RJ45_2/DIR1: R17.1, U4.2, U4.3
/RJ45_2/DIR2: R18.1, U5.2, U5.3
/RJ45_3/DIR1: R26.1, U6.2, U6.3
/RJ45_3/DIR2: R27.1, U7.2, U7.3
/RJ45_5/DIR1: R35.1, U8.2, U8.3
/RJ45_5/DIR2: R36.1, U9.2, U9.3
GND: C1.2, C2.2, C3.2, C4.2, C5.2, C6.2, C7.2, C8.2, C9.2, C10.2, C11.2, C12.2, C13.2, C14.2, C15.2, C16.2, C17.2, C18.2, C19.2, J1.4, J1.5, J5.10, J5.12, J5.14, J5.16, J5.18, J5.20, J5.22, J5.24, J5.26, J6.2, J7.3, J7.4, J8.2, J8.4, J13.4, J13.5, J14.4, J14.5, J15.4, J15.5, JP1.1, JP2.3, JP3.1, JP4.3, JP5.1, JP6.3, JP7.1, JP8.3, R1.2, R4.2, R7.2, R10.2, R13.2, R16.2, R19.2, R22.2, R25.2, R28.2, R31.2, R34.2, U1.2, U2.5, U3.5, U4.5, U5.5, U6.5, U7.5, U8.5, U9.5
GNDD: C4.1, C8.1, C12.1, C16.1, J1.13, J13.13, J14.13, J15.13, R1.1, R10.1, R19.1, R28.1
unnamed: C5.1, C6.1, J13.7, J13.8, JP1.3, JP2.1, L1.1, R2.1, R5.1, U2.8, U3.8
unnamed: C9.1, C10.1, J14.7, J14.8, JP3.3, JP4.1, L2.1, R11.1, R14.1, U4.8, U5.8
unnamed: C13.1, C14.1, J15.7, J15.8, JP5.3, JP6.1, L3.1, R20.1, R23.1, U6.8, U7.8
unnamed: C17.1, C18.1, J1.7, J1.8, JP7.3, JP8.1, L4.1, R29.1, R32.1, U8.8, U9.8
unnamed: J1.1, R29.2, R30.1, U8.6
unnamed: J1.2, R30.2, R31.1, U8.7
unnamed: J1.3, R32.2, R33.1, U9.6
unnamed: J1.6, R33.2, R34.1, U9.7
unnamed: J13.1, R2.2, R3.1, U2.6
unnamed: J13.2, R3.2, R4.1, U2.7
unnamed: J13.3, R5.2, R6.1, U3.6
unnamed: J13.6, R6.2, R7.1, U3.7
unnamed: J14.1, R11.2, R12.1, U4.6
unnamed: J14.2, R12.2, R13.1, U4.7
unnamed: J14.3, R14.2, R15.1, U5.6
unnamed: J14.6, R15.2, R16.1, U5.7
unnamed: J15.1, R20.2, R21.1, U6.6
unnamed: J15.2, R21.2, R22.1, U6.7
unnamed: J15.3, R23.2, R24.1, U7.6
unnamed: J15.6, R24.2, R25.1, U7.7
unnamed: JP1.2, R8.2
unnamed: JP2.2, R9.2
unnamed: JP3.2, R17.2
unnamed: JP4.2, R18.2
unnamed: JP5.2, R26.2
unnamed: JP6.2, R27.2
unnamed: JP7.2, R35.2
unnamed: JP8.2, R36.2

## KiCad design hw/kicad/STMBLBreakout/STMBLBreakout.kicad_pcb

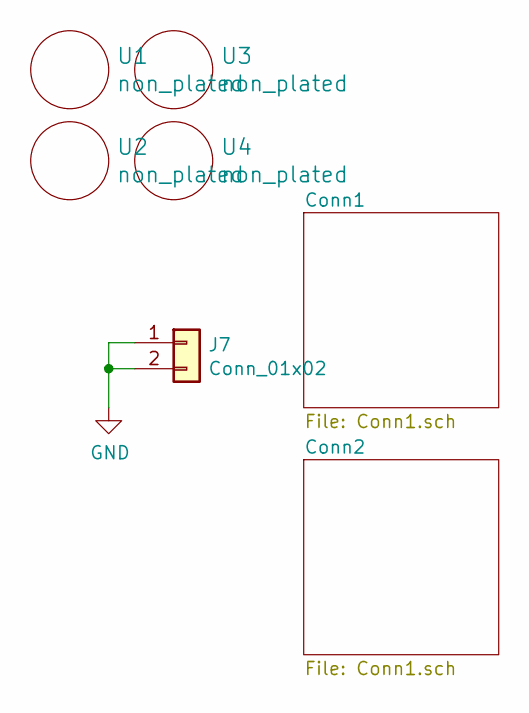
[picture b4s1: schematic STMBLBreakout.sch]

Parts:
J7: Conn_01x02; TerminalBlock_4Ucon_1x02_P3.50mm_Horizontal
U1, U2, U3, U4: non_plated; non_plated_3mm

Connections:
GND: J7.1, J7.2; also elsewhere on the board

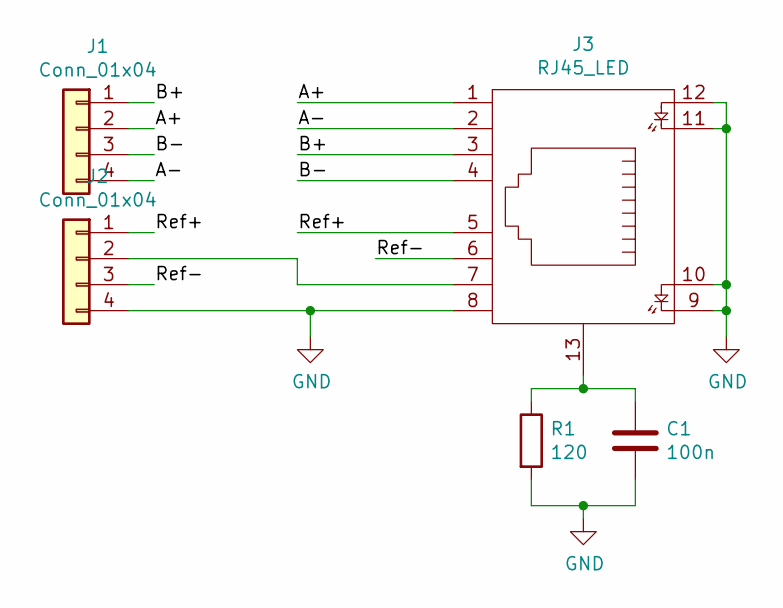
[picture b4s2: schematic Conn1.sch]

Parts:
C1: 100n; C_0805
J1, J2: Conn_01x04; TERMINAL_BLOCK_2PIN_3.5
J3: RJ45_LED
R1: 120; R_0805

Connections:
/Conn1/A+: J1.2, J3.1
/Conn1/A-: J1.4, J3.2
/Conn1/B+: J1.1, J3.3
/Conn1/B-: J1.3, J3.4
/Conn1/Ref+: J2.1, J3.5
/Conn1/Ref-: J2.3, J3.6
GND: C1.2, J2.4, J3.8, J3.9, J3.10, J3.11, J3.12, R1.2; also elsewhere on the board
unnamed: C1.1, J3.13, R1.1
unnamed: J2.2, J3.7

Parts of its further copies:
C2: 100n; C_0805
J4, J5: Conn_01x04; TERMINAL_BLOCK_2PIN_3.5
J6: RJ45_LED
R2: 120; R_0805

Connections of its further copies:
/Conn2/A+: J4.2, J6.1
/Conn2/A-: J4.4, J6.2
/Conn2/B+: J4.1, J6.3
/Conn2/B-: J4.3, J6.4
/Conn2/Ref+: J5.1, J6.5
/Conn2/Ref-: J5.3, J6.6
GND: C2.2, J5.4, J6.8, J6.9, J6.10, J6.11, J6.12, R2.2; also elsewhere on the board
unnamed: C2.1, J6.13, R2.1
unnamed: J5.2, J6.7

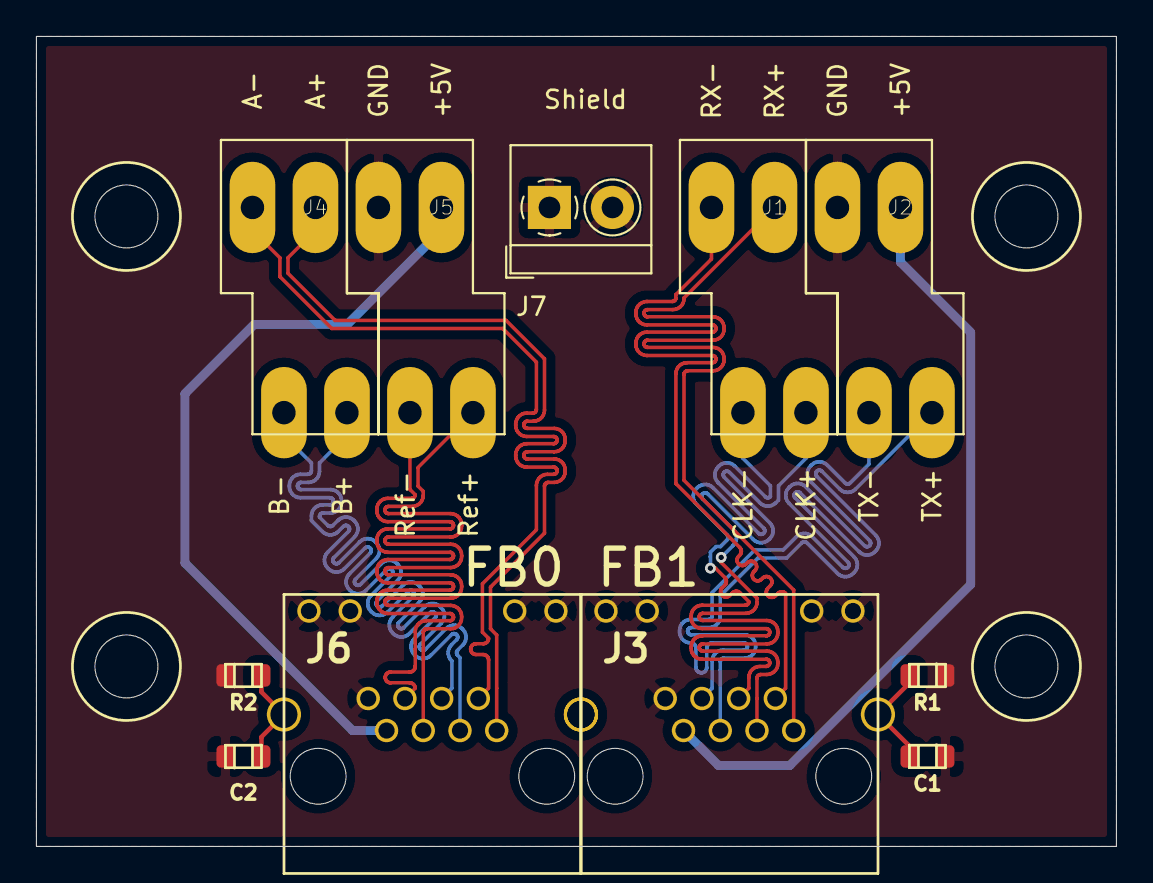
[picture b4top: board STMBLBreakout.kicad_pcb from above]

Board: 2 copper layers, 60.0 x 45.0 mm, 15 parts (0 on the bottom side), 17 nets.
